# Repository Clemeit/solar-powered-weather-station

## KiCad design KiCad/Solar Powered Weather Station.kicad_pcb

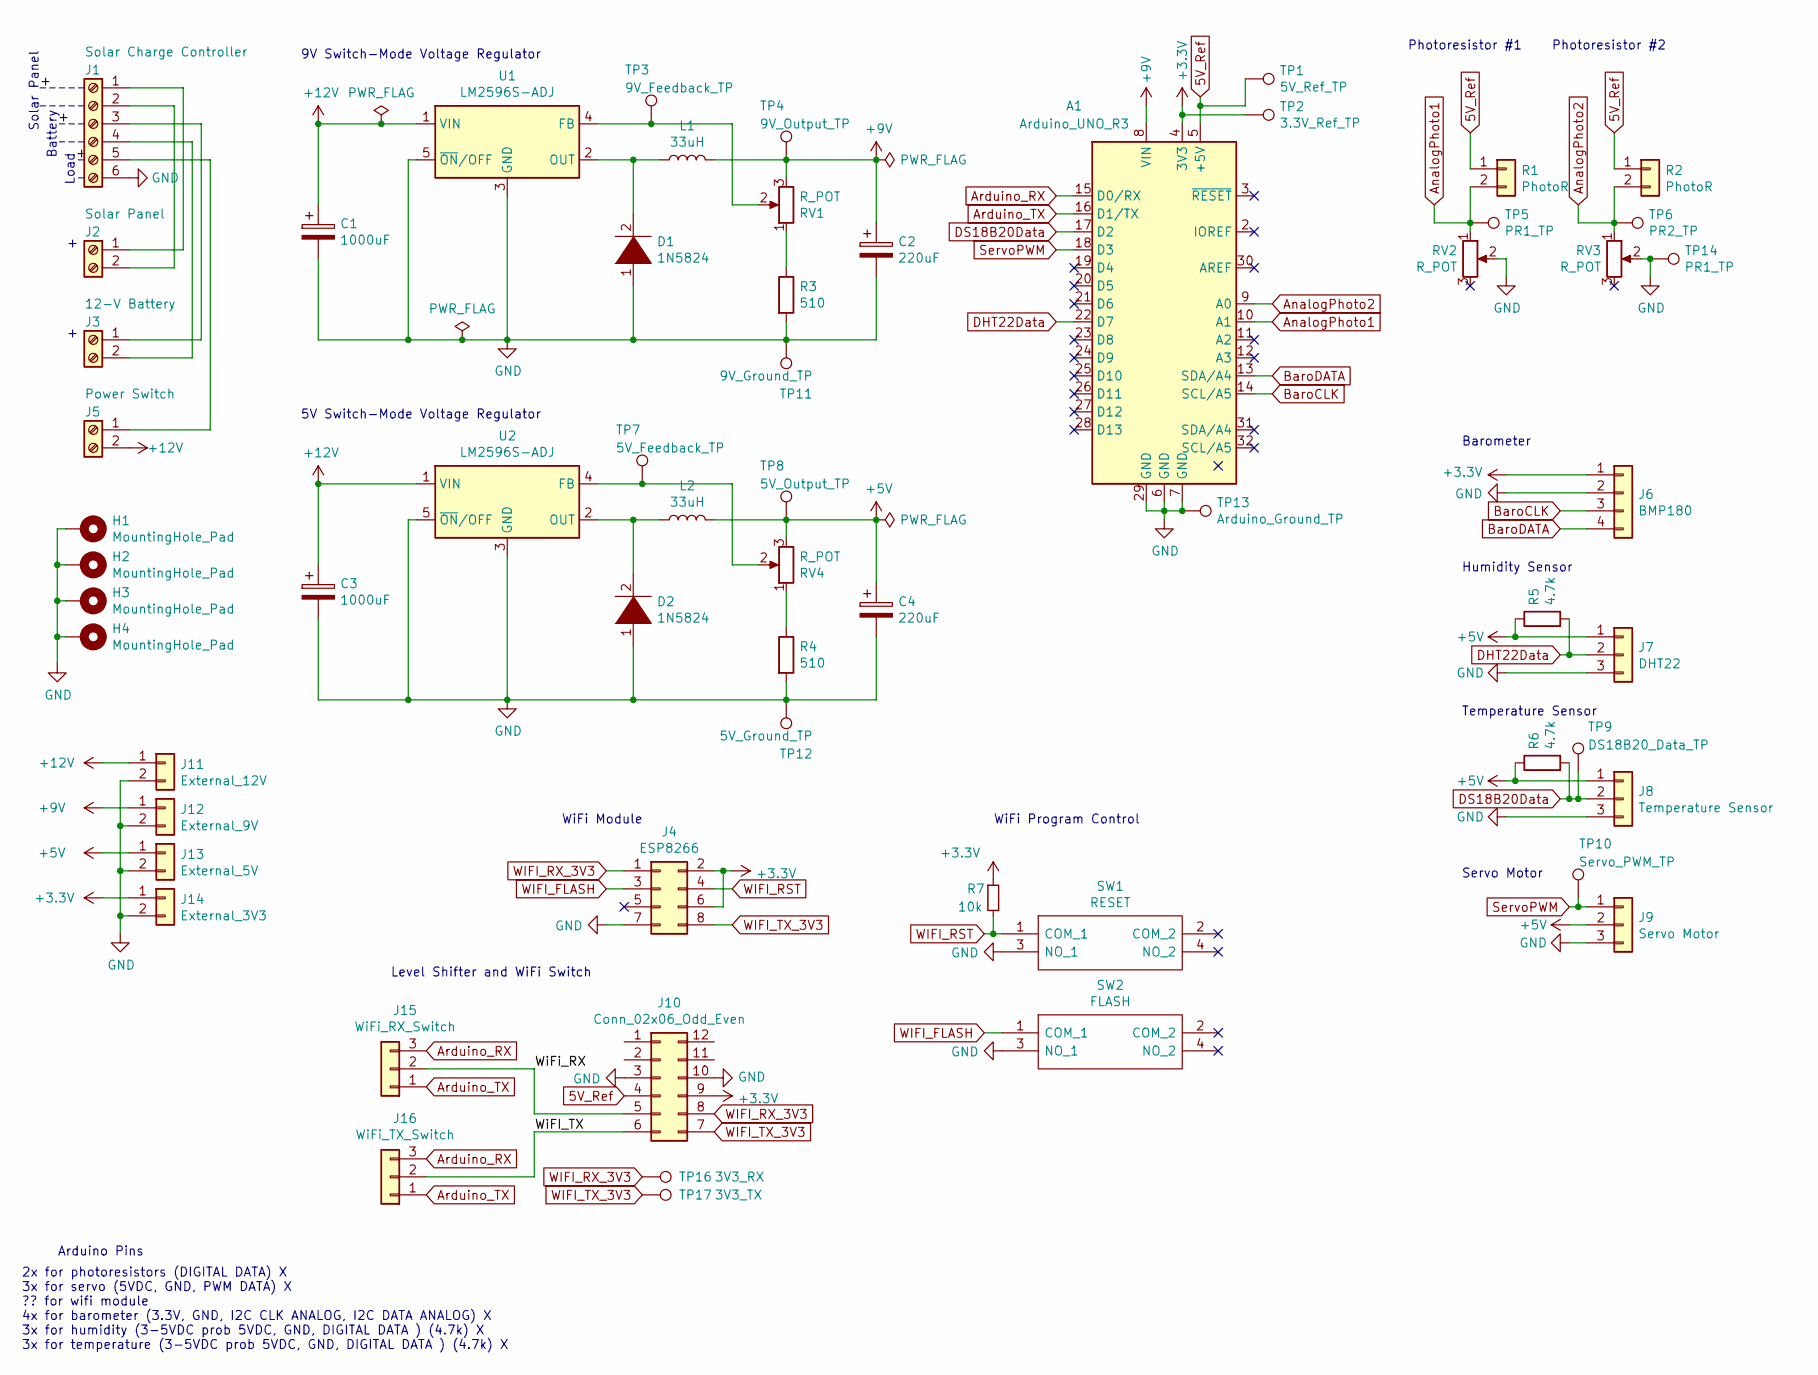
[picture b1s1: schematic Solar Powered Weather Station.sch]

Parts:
A1: Arduino_UNO_R3
C1, C3: 1000uF; CP_Radial_D10.0mm_P3.50mm
C2, C4: 220uF; CP_Radial_D8.0mm_P2.50mm
D1, D2: 1N5824; D_5W_P12.70mm_Horizontal
H1, H2, H3, H4: MountingHole_Pad; TestPoint_Plated_Hole_D4.0mm
J1: Solar Charge Controller; TerminalBlock_Phoenix_MKDS-1,5-6-5.08_1x06_P5.08mm_Horizont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
J2: Solar Panel; TerminalBlock_Phoenix_MKDS-1,5-2-5.08_1x02_P5.08mm_Horizont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
J3: 12-V Battery; TerminalBlock_Phoenix_MKDS-1,5-2-5.08_1x02_P5.08mm_Horizont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
J4: ESP8266; PinHeader_2x04_P2.54mm_Vertical
J5: Power Switch; TerminalBlock_Phoenix_MKDS-1,5-2-5.08_1x02_P5.08mm_Horizont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
J6: BMP180; PinHeader_1x04_P2.54mm_Vertical
J7: DHT22; PinHeader_1x03_P2.54mm_Vertical
J8: Temperature Sensor; PinHeader_1x03_P2.54mm_Vertical
J9: Servo Motor; PinHeader_1x03_P2.54mm_Vertical
J10: Conn_02x06_Odd_Even; Level_shifter
J11: External_12V; PinHeader_1x02_P2.54mm_Vertical
J12: External_9V; PinHeader_1x02_P2.54mm_Vertical
J13: External_5V; PinHeader_1x02_P2.54mm_Vertical
J14: External_3V3; PinHeader_1x02_P2.54mm_Vertical
J15: WiFi_RX_Switch; PinHeader_1x03_P2.54mm_Vertical
J16: WiFi_TX_Switch; PinHeader_1x03_P2.54mm_Vertical
L1, L2: 33uH; L_Axial_L7.0mm_D3.3mm_P10.16mm_Horizontal_Fastron_MICC
R1, R2: PhotoR; PinHeader_1x02_P2.54mm_Vertical
R3, R4: 510; R_Axial_DIN0207_L6.3mm_D2.5mm_P7.62mm_Horizontal
R5, R6: 4.7k; R_Axial_DIN0207_L6.3mm_D2.5mm_P7.62mm_Horizontal
R7: 10k; R_Axial_DIN0207_L6.3mm_D2.5mm_P7.62mm_Horizontal
RV1, RV2, RV3, RV4: R_POT; Potentiometer_Bourns_3296W_Vertical
SW1: RESET; LL3301FF065QJ
SW2: FLASH; LL3301FF065QJ
TP1: 5V_Ref_TP; TestPoint_Plated_Hole_D2.0mm
TP2: 3.3V_Ref_TP; TestPoint_Plated_Hole_D2.0mm
TP3: 9V_Feedback_TP; TestPoint_Plated_Hole_D2.0mm
TP4: 9V_Output_TP; TestPoint_Plated_Hole_D2.0mm
TP5, TP14: PR1_TP; TestPoint_Plated_Hole_D2.0mm
TP6: PR2_TP; TestPoint_Plated_Hole_D2.0mm
TP7: 5V_Feedback_TP; TestPoint_Plated_Hole_D2.0mm
TP8: 5V_Output_TP; TestPoint_Plated_Hole_D2.0mm
TP9: DS18B20_Data_TP; TestPoint_Plated_Hole_D2.0mm
TP10: Servo_PWM_TP; TestPoint_Plated_Hole_D2.0mm
TP11: 9V_Ground_TP; TestPoint_Plated_Hole_D2.0mm
TP12: 5V_Ground_TP; TestPoint_Plated_Hole_D2.0mm
TP13: Arduino_Ground_TP; TestPoint_Plated_Hole_D2.0mm
TP16: 3V3_RX; TestPoint_Plated_Hole_D2.0mm
TP17: 3V3_TX; TestPoint_Plated_Hole_D2.0mm
U1, U2: LM2596S-ADJ; TO-262-5_Vertical

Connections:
5V_Ref: A1.5 (+5V), J10.4, R1.1, R2.1, TP1.1
+3V3: A1.4 (3V3), J4.2, J4.6, J6.1, J10.9, J14.1, R7.1, TP2.1
+5V: C4.1, J7.1, J8.1, J9.2, J13.1, L2.2, R5.1, R6.1, RV4.3, TP8.1
+9V: A1.8 (VIN), C2.1, J12.1, L1.2, RV1.3, TP4.1
+12V: C1.1, C3.1, J5.2, J11.1, U1.1 (VIN), U2.1 (VIN)
/WiFI_TX: J10.6, J16.2
/WiFi_RX: J10.5, J15.2
AnalogPhoto1: A1.10 (A1), R1.2, RV2.1, TP5.1
AnalogPhoto2: A1.9 (A0), R2.2, RV3.1, TP6.1
Arduino_RX: A1.15 (D0/RX), J15.3, J16.3
Arduino_TX: A1.16 (D1/TX), J15.1, J16.1
BaroCLK: A1.14 (SCL/A5), J6.3
BaroDATA: A1.13 (SDA/A4), J6.4
DHT22Data: A1.22 (D7), J7.2, R5.2
DS18B20Data: A1.17 (D2), J8.2, R6.2, TP9.1
GND: A1.6 (GND), A1.7 (GND), A1.29 (GND), C1.2, C2.2, C3.2, C4.2, D1.1 (K), D2.1 (K), H1.1, H2.1, H3.1, H4.1, J1.6, J4.7, J6.2, J7.3, J8.3, J9.3, J10.3, J10.10, J11.2, J12.2, J13.2, J14.2, R3.2, R4.2, RV2.2, RV3.2, SW1.3 (NO_1), SW2.3 (NO_1), TP11.1, TP12.1, TP13.1, TP14.1, U1.3 (GND), U1.5 (~ON~/OFF), U2.3 (GND), U2.5 (~ON~/OFF)
unnamed: D1.2 (A), L1.1, U1.2 (OUT)
unnamed: D2.2 (A), L2.1, U2.2 (OUT)
unnamed: J1.1, J2.1
unnamed: J1.2, J2.2
unnamed: J1.3, J3.1
unnamed: J1.4, J3.2
unnamed: J1.5, J5.1
unnamed: R3.1, RV1.1
unnamed: R4.1, RV4.1
unnamed: RV1.2, TP3.1, U1.4 (FB)
unnamed: RV4.2, TP7.1, U2.4 (FB)
ServoPWM: A1.18 (D3), J9.1, TP10.1
WIFI_FLASH: J4.3, SW2.1 (COM_1)
WIFI_RST: J4.4, R7.2, SW1.1 (COM_1)
WIFI_RX_3V3: J4.1, J10.8, TP16.1
WIFI_TX_3V3: J4.8, J10.7, TP17.1

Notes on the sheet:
Arduino Pins
2x for photoresistors (DIGITAL DATA) X 3x for servo (5VDC, GND, PWM DATA) X ?? for wifi module 4x for barometer (3.3V, GND, I2C CLK ANALOG, I2C DATA ANALOG) X 3x for humidity (3-5VDC prob 5VDC, GND, DIGITAL DATA ) (4.7k) X 3x for temperature (3-5VDC prob 5VDC, GND, DIGITAL DATA ) (4.7k) X
Photoresistor #1
Photoresistor #2
5V Switch-Mode Voltage Regulator
9V Switch-Mode Voltage Regulator
Solar Panel
Battery
Load
WiFi Module
Humidity Sensor
Temperature Sensor
Servo Motor
Barometer
Level Shifter and WiFi Switch
WiFi Program Control

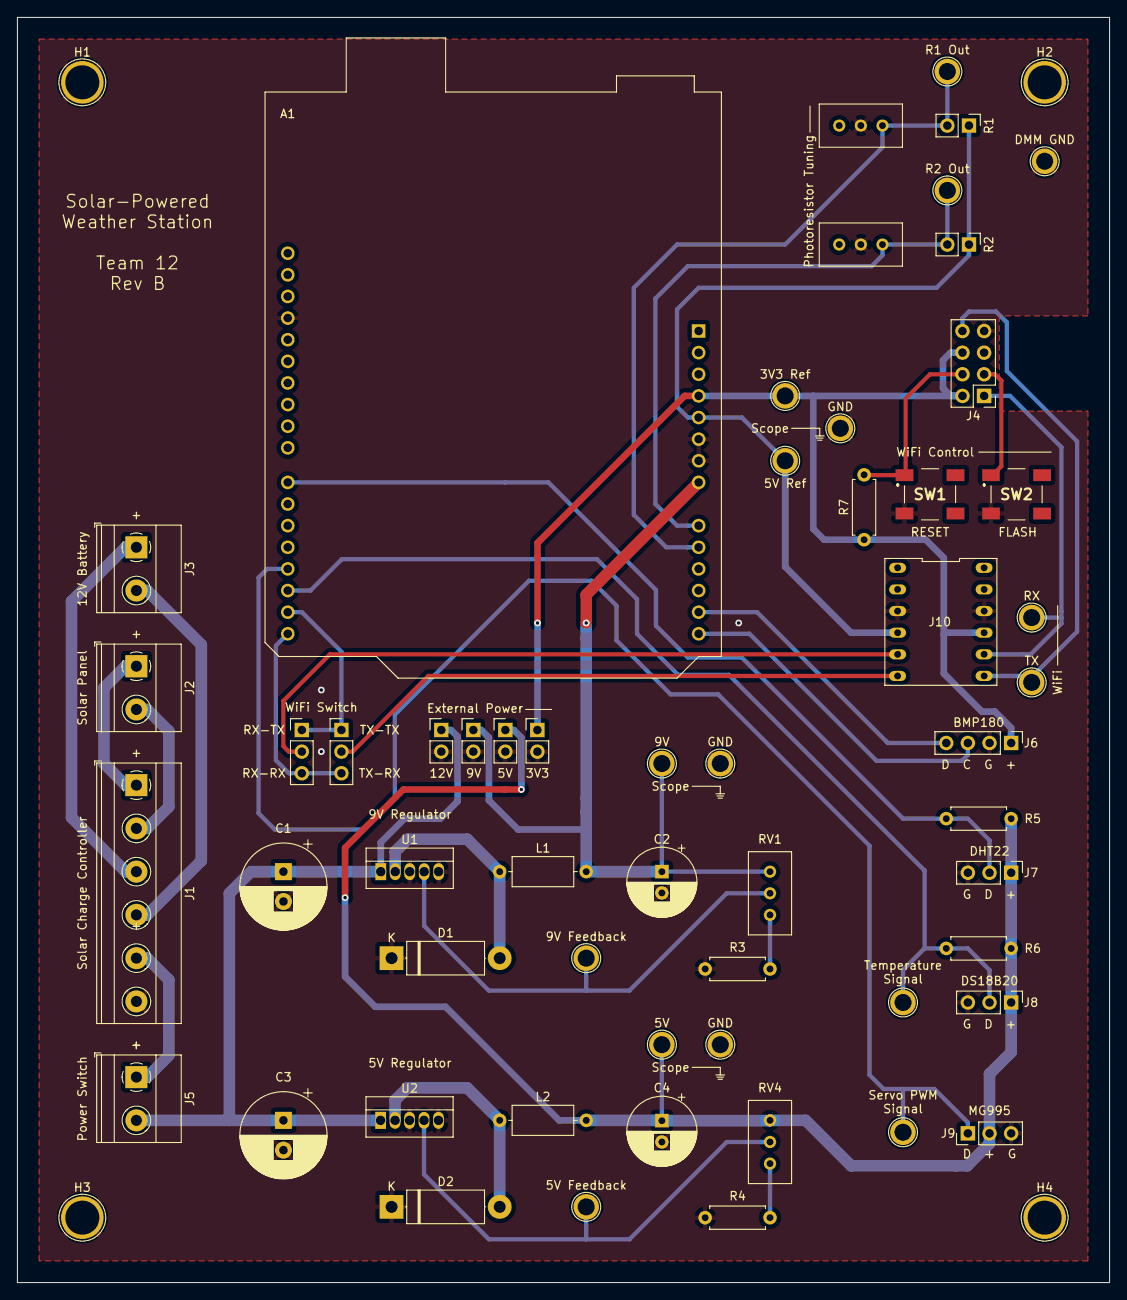
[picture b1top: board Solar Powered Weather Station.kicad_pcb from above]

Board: 2 copper layers, 128.3 x 148.6 mm, 60 parts (0 on the bottom side), 32 nets.

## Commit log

2021-10-15 MG995 Photoresistor code reformatting
2021-10-15 Created DHT22 sensor test
2021-10-15 Created BMP180 sensor test
2021-10-15 Created full sensor integration test
2021-10-15 Minor BMP180 changes
2021-10-21 Periodically run servo
2021-10-21 Created Final Sketch
2021-10-24 Added KiCad files
2021-10-24 Updated PCB
2021-10-29 Create Libraries
2021-11-15 Final code changes for serial communication
2021-11-15 Working sketch for the ESP module
    This code reads weather data over serial communication and outputs it to a webpage.
2021-11-16 Final sketch for the ESP01S module
    This code should be uploaded to the ESP-01S module, NOT the Arduino Uno. This sketch creates an access point and serves a webpage containing weather data gathered from the Arduino Uno over serial com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
2021-11-18 Updated ESP code
2021-11-18 Handle servo on a loop
2021-11-18 Final sketch for the Arduino Uno
    This sketch should be uploaded to the Arduino Uno ONLY. This code reads sensor data and outputs the result over serial.
2021-11-18 Ready for demo
